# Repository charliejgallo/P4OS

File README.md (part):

# P4OS

An iPhone-style operating system for the
[**Waveshare ESP32-P4-WIFI6-Touch-LCD-5**](https://www.waveshare.com/esp32-p4-wifi6-touch-lcd-5.htm)
([wiki](https://docs.waveshare.com/ESP32-P4-WIFI6-Touch-LCD-5)). It is a 5"
720×1280 touch board with an ESP32-P4 (two RISC-V cores at 400 MHz and
32 MB of PSRAM) and an ESP32-C6 that does the Wi-Fi, the Bluetooth and,
since 0.34, the Zigbee radio.

It has a home screen with pages, folders and a dock, a control centre and
notifications, and a lock screen with an optional code, and it runs in
portrait or landscape. There are twenty-five built-in apps and, since
0.30, a **Store** that installs more than eighty others on the microSD,
loaded as shared objects:

- **A store of its own:** the board lists, installs and updates its apps
  from a catalogue published with each release, and fetches its own next
  firmware. Other people's repositories can be added beside the official
  one.

- **Games:** thirty-five, among them Mila (a Sokoban with a black cat in
  Blender 3D), Monster Hop, a racing game, golf, a robot RPG, a 3D pinball
  with six tables, a tower defense over ten worlds, a pipes game with six
  liquids, Doom at 35 fps and Duke Nukem 3D; and an emulator of
  fourteen consoles, the Game Boy Advance and the Neo Geo at full speed.
- **Tools:** notes with task lists, a street map with offline zones,
  internet radio, IP cameras, video, a 3D viewer, a tuner, a drawing app,
  a VNC viewer for a computer's screen, every 3D printer in the house
  (OctoPrint, PrusaLink, Bambu Lab, Klipper, Duet, Elegoo, FlashForge,
  Creality) with its camera, a computer algebra system with
  graphs, geometry and statistics, a data logger for the header's sensors,
  Lua, and Python (MicroPython).
- **A web portal** for files, updates, the log and the network sweeps, and a
  page for every app that wants one, which the app brings from the card;
  since 0.35 a phone on the portal is also a gamepad.
- **Messages, since 0.35:** Telegram with your own account (MTProto written
  in C), mail over IMAP and SMTP, a Meshtastic client, and **a Telegram bot
  of the board's own** that answers in a chat and sends what its rules say
  (a door opened, a screenshot at an hour). [docs/BOT.md](docs/BOT.md).
- **Cameras, since 0.35:** a USB webcam as a security camera that records
  H.264 when something moves and is an RTSP camera for Frigate, and as a
  camera that sees (faces, people, objects, hands, QR and barcodes) with
  Espressif's esp-dl on the board.
- **Bluetooth with the phone:** the iPhone's notifications on the board, in
  colour emoji, its music, and its calls answered or rejected from the
  board; and the board as a computer's wireless keyboard and mouse.
- **USB:** the port becomes a keyboard, mouse, gamepad, MIDI device, network
  or disk for a computer; and the board is a USB host on its 40-pin header,
  two ports at once: pendrives, keyboards, mice, gamepads, webcams, sound
  cards, MIDI and serial devices.
- **A Wi-Fi network of its own,** joined with a QR code.
- **Ethernet, for a board that has the module:** a W5500 on the header,
  and tools for a wired bench: a tester for a network port, finding a
  device of unknown address, a capture for Wireshark.
- **The workshop:** I2C, SPI, 1-Wire and GPIO on the 40-pin header, with
  112 kinds of sensor read by themselves (temperature, pressure, air
  quality, light, motion, current, distance...), addressable LED strips on
  any free pin (WLED's way), a serial terminal, an ESP32, Arduino and SWD programmer,
  RS485 with a Modbus tester (master, slave, monitor, a TCP gateway) and
  DMX512 (a test console, an analyzer, RDM, an Art-Net and sACN node, and a
  lighting console for a phone), a bench supply and scope, an EEPROM reader and writer, a PWM and
  servo generator with an analog level (and sixteen more servos on a
  PCA9685), a learning
  infrared remote with SmartIR's codes, a CAN bus analyser, and a logic
  analyser with ten protocol decoders for the 24 MHz USB boxes or an
  ESP32 with its own firmware. Each one was tried on the bench with real
  parts, wiring diagrams and photos included.
- **Zigbee, since 0.34:** the board is a **Zigbee hub** of its own, where
  almost any device can be joined and tried (sensors, relays, dimmers,
  Tuya devices, IR blasters), and it can **pose as a device** on Home
  Assistant's network (ZHA or Zigbee2MQTT) to test the coordinator; both
  from the board or from a phone through the portal. [More below](#zigbee-a-hub-a-test-bench-and-a-fake-device).
- **Drawn icons, since 0.34:** two packs, 3D toy and Line, as System parts
  in the Store; the usual circles stay a choice.
- **A software radio:** an RTL-SDR stick on the USB host gives a live
  spectrum and waterfall, broadcast FM in stereo, AM for the airband and
  narrow FM for hams and PMR, and the 433/868 MHz remotes and weather
  sensors decoded, with recordings of all of it and a page in the portal.

A desktop simulator runs the same UI code, so most of it can be built and
tried without the board.

It descends from [AmoledOS](https://github.com/charliejgallo/ESP32S3_AmoledOS),
a smartwatch firmware for a 1.8" board. The app model, the portal and many
of the apps came from there, redrawn for a screen five times larger.

<p align="center"><em>The captures come from the simulator, which draws the
same pixels as the board.</em></p>

## Getting started

A new board needs a cable once, and nothing after that.

1. **Flash it.** `esptool.py --chip esp32p4 chip_id` says which silicon the
   board has; download `p4os-rev1_3-full.zip` (chip v1.x) or
   `p4os-rev3_x-full.zip` (v3.x) from the
   [latest release](https://github.com/charliejgallo/P4OS/releases/latest),
   unpack it and, from inside the folder,
   `esptool.py --chip esp32p4 -p <port> write_flash @flash_args`.
2. **Put a microSD in**, formatted as FAT32. An empty one is fine.
3. **Join the Wi-Fi** in Settings → Networks, and pick the language.
4. **Open the Store** and get the apps you want. They install and open
   with no restart; a game's art comes in packs, the extra ones chosen on
   its page.
5. **Later versions arrive by themselves:** the Store updates the apps,
   and Settings → Update fetches the next firmware from GitHub, checks it
   and installs it on a tap.

| The Store | An app's page | Its description and extras | Settings, Update |
|---|---|---|---|
|  |  |  |  |

[docs/INSTALL.md](docs/INSTALL.md) is the whole of it, step by step: a new
board from nothing, a board coming from 0.2x, and adding apps.
[docs/STORE.md](docs/STORE.md) is the Store itself: what it checks, other
people's sources and what adding one means, and what a catalogue is made
of.

**Coming from 0.2x?** Update the firmware once more the old way (the
portal's Firmware page, with `p4os-<rev>.bin`). Nothing has to be copied to
the card: the apps that are there go on working, and Store → Installed
offers to take them over so they update from then on.

<p align="center"><em>And on the board: a BME280 on the rear header, found by
itself in Modules and by the scan in Bus, and the SPI loopback at 40 MHz
(that one is a capture from the panel, over HTTP).</em></p>

<p align="center"><em>A MAX6675 with a type K thermocouple on the SPI port:
Bus's example reads it, and Modules logs it every second; the curve is the
tip heated with a lighter.</em></p>

<p align="center"><em>A Pimoroni BME688 on i2c.ext: Bus lists what may live at
0x76, and Modules recognises it by itself as a BME688 (not a BME680), with
its gas resistance, which fell to half with alcohol near it and came back.</em></p>

<p align="center"><em>An SCD41 found by itself at 0x62: the chart is the CO2
of a breath on it, from 3000 ppm back to the room's 600.</em></p>

<p align="center"><em>The Programmer reading the whole flash of an AmoledOS
watch (an ESP32-S3 on its own USB) to the card, and writing it back: the
watch came back with every setting it had.</em></p>

<p align="center"><em>And by SWD, three wires to a Pico's debug header: the
RP2040 found behind its multidrop port and a new firmware written and
verified in under half a second.</em></p>

<p align="center"><em>A cheap Wi-Fi camera (a Hi3518EV200) opened up, its
console pads soldered to the header: U-Boot stopped with a mix of keys and its
16 MB read out through its own commands, twice, with the same SHA-256 -
the copy kept before giving it a new firmware.</em></p>

<p align="center"><em>The Ekoparty 2026 badge (an nRF52840 running
Meshtastic) read whole by SWD in 8 seconds, and an Arduino Nano from a
drawer on the USB host: written by the Programmer, then talking in the
Terminal.</em></p>

<p align="center"><em>A Blue Pill by SWD: its chip a clone (DPIDR 2BA01477,
a CKS32) with 128 KB that really are there. Read whole in a second, written
and erased; and the same again through ST's serial bootloader on the same
two wires.</em></p>

<p align="center"><em>An ESP32 DevKit on the header with six wires: the
board resets it into its ROM by itself and writes it at up to 921600 baud;
the Mac's esptool does the same through the board's bridge.</em></p>

<p align="center"><em>The same Nano, now on the header: its 5 V TX through
a divider, the EN line on its reset. Written and read by the Flasher, and
by avrdude on the Mac through the bridge.</em></p>

<p align="center"><em>A Mega 2560 from an old 3D printer and a Pro Micro on
the USB host: the Mega's own bootloader, and the Pro Micro's, reached with
the 1200-baud touch.</em></p>

<p align="center"><em>An Arduino Yún: its Linux in the Terminal through the
32U4, and its old U-Boot (no sf, no crc32, a big-endian MIPS) read whole by
the Programador, the same MD5 its Linux gives.</em></p>

<p align="center"><em>A WH5000 multimeter through its own USB cable (a
CP2102 inside), at 2400 baud: one line a reading, the digits on its
display. Any speed from 50 baud and any frame, 7E1 included, since
0.33.0.</em></p>

<p align="center"><em>Ethernet: a W5500 Lite on the header with six loose
wires, and Network's Cable tab telling what the port it is plugged into
gives (the network's addresses are blurred).</em></p>

---

## What it does

### The shell

The home screen has icon pages, folders, a dock and widgets.

- **Arranging it** is as on an iPhone. A long press starts edit mode, where
  a swipe still turns the page and an icon held still for a moment drags:
  - onto another page;
  - onto another app, to make a folder;
  - into a folder;
  - in or out of the dock, where the icons drag the same way.

  Folders show twelve apps a page, and a swipe turns one whole page. The
  portal's `#inicio` page does the same from a computer.

- **Widgets** (on the board since 0.22.0): edit mode's **+ Widget** adds
  the clock, the sensors, Home Assistant, the system monitor or Claude's
  usage; a tap on a widget opens its sheet, with its size (2×2, 4×2, 4×4),
  what it shows and a way to take it off, and one held still for a moment
  drags like an icon. The **sensors widget** shows up to six of the sensor
  service's values (on its own CO₂, temperature, humidity, pressure and the
  like; CO₂ and particles coloured by their level), the **Home Assistant**
  one up to eight entities, the favourites or the ones picked.

- **Swiping down** from the top opens the control centre (Wi-Fi, Bluetooth,
  do not disturb, the system sounds, orientation, brightness, volume, the
  music playing on the board or on the iPhone, the screen recording) and the
  notifications, with the phone's own actions.
- **System sounds:** a few notes of the speaker's bell when locking and
  unlocking, for notifications and calls, screenshots and recordings, and an
  optional keyboard click. The control centre's bell turns them all off.
- **Recording the screen** (since 0.21.5): the control centre's Grabar
  button records what the panel shows to an MP4 on the card (`/videos`),
  games and cameras included, with a red dot in the status bar while it
  runs. The P4's own engines do the work: the PPA turns each frame into
  the encoder's YUV, the hardware H.264 encoder compresses it (70 ms a
  frame between them, 15 fps on a quiet screen and 7-9 while apps move),
  and the CPU mostly waits. It plays on a Mac or a phone as it is.
- **Typing** (since 0.24.0): the field being edited shows a blinking cursor
  and a ring in the accent colour. The keyboard has an ñ, holding a key
  opens its accents (á, ü, ñ, ¿...), shift gives one capital or locks with
  two taps, and dragging along the space bar moves the cursor. Holding a
  field selects, cuts, copies and pastes; the clipboard is shared with the
  apps and with the portal, which can type a long password or an address
  straight into the field open on the board.
- **Search** (since 0.24.0): a swipe down from the middle of the home screen
  finds apps, the pages of Settings, notes by their text and the card's
  files, and works out a sum typed in.
- **The App Library** (since 0.35): the home screen's last page has every
  app, those taken off the home screen too, in the Store's categories: a
  card each with three apps big and a cluster of the rest that opens the
  whole category. Its pictures are made only while it is on screen.
- **The status bar** shows the Wi-Fi or the board's own network, the card
  and the USB, and the services working in the background: the Zigbee
  radio in a colour for each mode (its own network, open to join,
  emulating a device, scanning), the Telegram bot, Datalog logging, a 3D
  printer printing.
- **The orientation** is chosen in Settings or the control centre, because
  the board has no accelerometer. Apps that only make sense one way turn the
  screen while they are open.
- **The BOOT button** goes home with a tap and takes a screenshot with a long
  press; screenshots go to an album in Photos. Held during the boot screen,
  it starts in safe mode, without the card's apps.

| Settings in landscape | Macro pad | Photos |
|---|---|---|
|  |  |  |

<p align="center">
  
</p>

<p align="center"><em>Recorded by the board itself with its control
centre's button: the home screen, a folder, Photos.</em></p>

### The lock screen

It shows the time and date large, the messages that came in, and the music
playing with its buttons, over the wallpaper. To unlock, swipe up from
anywhere: the screen follows the finger.

- **When it locks:** at boot, and when the screen has been off for the time
  chosen in Settings (as soon as it goes off, or 1, 5, 15 or 60 minutes
  later). It is checked while the screen is still dark, so waking never
  shows a frame of what was under it.
- **An optional code** of 4 or 6 digits. It is kept as a salted SHA-256,
  never as itself. After 5 wrong tries the pad waits 30 s, and twice as long
  every 3 more; the count survives a restart.
- **A forgotten code:** in the BOOT button's safe mode the lock screen
  does not ask for it, and Settings can remove it.
- **Messages:** the notifications, the apps', the iPhone's over Bluetooth
  and Home Assistant's, in one list. With a code, their text can stay
  hidden until unlocked.
- **Widgets** (since 0.35): up to three capsules under the date, chosen in
  Settings, Lock screen: the next alarm, the sensors, the Zigbee network
  and its devices. Each shows only when it has something to say.

| Locked | With widgets | The code | Settings, Wi-Fi: its own network |
|---|---|---|---|
|  |  |  |  |

### Wallpapers

Eight gradients and a ninth that follows the time of day (night, dawn, day,
dusk, a little different every minute), and over them a photo from the card for the home screen
and another for the lock screen, chosen from Photos (the palette at the top
right of a photo). Each is cropped to the screen, kept in PSRAM (1.8 MB a
screen, nothing in internal RAM) and darkened as much as its own
brightness asks, once, while it is decoded, so the white names read on it
with no translucent layer to blend each frame. Turning the screen crops it
again; Settings, Wallpaper shows which photo each has and removes it.
The lock screen can take a whole folder instead (since 0.22.0): another of
its photos, at random, every time the board locks. The home screen's photo
stays in PSRAM with an app in front, so going home shows it at once; the
lock screen's is let go and decoded again as the screen goes dark.

| Home, over a photo | Locked, over another |
|---|---|
|  |  |

<p align="center"><em>Both on the board, both of Mila.</em></p>

The same page picks the **accent colour** (switches, selections, the active
buttons), one of iOS's nine system colours. The lock screen's clock is
large or medium, at the top or in the middle, and white, the accent, or the
lock photo's own colour lightened (Settings, Lock screen).

The gesture is a free swipe up, as phones do it today, and not a control
dragged along a track: Apple's 2005 patent on the latter
([US 7,657,849](https://patents.google.com/patent/US7657849B2)) expired in
2025, but that is not the reason this one was chosen.

### Built-in apps

Every day:

| Files | Photos | Music | Clock | Calendar |
|---|---|---|---|---|
|  |  |  |  |  |

| Calculator | Converter | Home Assistant | Claude | Monitor |
|---|---|---|---|---|
|  |  |  |  |  |

- **Files:** the card's explorer, with search, copy, move and folders;
  firmware opens straight in the Programmer, documents in Office and
  videos in Video.
- **Photos:** albums, the screenshots among them.
- **Music:** MP3, gapless, with the covers.
- **Clock:** world clock, alarms, stopwatch, timer and pomodoro.
- **Home Assistant:** favourites and the calendar, over its WebSocket API.
- **Claude:** the usage of your own Claude plan, the numbers Claude Code's
  `/usage` shows. It is unofficial; see [CLAUDE-APP.md](docs/CLAUDE-APP.md).
- **Monitor:** CPU per core, the tasks, memory, temperature and the network.
- **Bot** (since 0.35): the board's own Telegram bot, its token, the chats
  linked with a code, the commands it answers and the rules that make it
  write or act by itself ([docs/BOT.md](docs/BOT.md)).
- **Also built in:** MQTT, Conway's Life, and Network, which has its own
  section below.

### Network, the tools for a network

Red in Spanish. Seven tabs; the first four work over any network, the
next two are for the wire ([Ethernet](#connected)), and the last for both.

| Cable | The switch, the traffic | Device | One device | Lookout |
|---|---|---|---|---|
|  |  |  |  |  |

- **Ping, Hosts, WiFi, mDNS:** latency and loss charted; a sweep of the
  network with every MAC and its maker, and a port scan; the Wi-Fi
  channels; the services announced. Each sweep is saved, and the portal
  compares it with the one before.
- **Cable** (since 0.27): a tester for the network port the board is
  plugged into.
  - What the port gives: speed and duplex, the address, the DHCP server
    and its lease.
  - "Test the way out": the gateway, a name, the internet, one after the
    other.
  - The switch: a managed one says its name, the port and the VLAN this
    cable goes to (LLDP or CDP).
  - "Compare": ten pings to the gateway by the wire and ten by the Wi-Fi,
    side by side. "Measure the speed" counts what `iperf -c` sends from a
    computer.
  - "Capture to the card": every frame that reaches the port, in a pcap
    file for Wireshark, and a warning for what a network should not have:
    two DHCP servers, one address claimed twice, a broadcast storm.
- **Device** (Equipo, since 0.27): for a device plugged straight into the
  board, its address unknown.
  - It listens: a device gives itself away as it starts (ARP, DHCP, mDNS,
    NetBIOS, SSDP, WS-Discovery). A sweep by ARP of the networks devices
    come set to finds the one that says nothing.
  - A tap opens the device: everything it said, who made its network card
    (with the IEEE's register on the card), a ping, a scan of its ports,
    and "Get on its network", which gives the wire an address next to its
    own.
  - The bench network: the board gives addresses out by DHCP, serves
    files by TFTP, the time by NTP and takes the device's syslog, on the
    wire only. "Share the Wi-Fi" also gives the device a way out through
    the board's Wi-Fi.
- **Lookout** (Vigía, since 0.27): a list of the bench's devices, which
  are on (a ping or a TCP port, every ten seconds while the tab is open),
  and Wake-on-LAN for the ones that are off.

What ran on the board and what did not is under
[What was tested](#what-was-tested-and-what-not-yet);
[docs/MODULES.md](docs/MODULES.md), "Ethernet", has each tool.

### The workshop

The 40-pin rear header is described in `modules.txt`: which pins make each
port (`i2c.ext`, `spi.a`, `uart.*`, GPIO) and which modules hang from them.
While an app uses a port it owns it, and Settings, Expansion draws the
header with who holds each pin.

The whole header, pin by pin, is under [The hardware](#the-40-pin-header).

| Bus (I2C scan) | Modules | Terminal | Programmer | Equipos (Riden) | Electronics |
|---|---|---|---|---|---|
|  |  |  |  |  |  |

- **Bus:** scans I2C and names what answers, talks to SPI chips with presets
  (flash memories, the MAX31855 and MAX6675 thermocouples, the MCP3008, the
  RC522 RFID reader, a loopback), finds the DS18B20s on a 1-Wire bus and reads them live with
  their resolution, and reads and drives GPIO.
- **LED Strips:** an addressable strip (WS2812B, WS2811, SK6812, SK6812 RGBW)
  on any free pin of the header, with the colour order and the number of
  LEDs. It has 13 effects with speed, intensity and two colours. The power
  tab estimates what the strip draws, WLED's way, and dims the whole frame to
  stay within the supply's budget. The strip keeps running with the app
  closed and comes back after a restart.
- **Modules:** live readings from 112 kinds of sensor, every second with
  five minutes of history (since 0.20): temperature and humidity, pressure,
  air quality (CO2, VOC, particles), light and colour, motion and compass,
  voltage and current, distance and presence. The I2C ones that can tell
  who they are are found by themselves (BME280/680, SHT, AHT, SCD4x, SGP30,
  VEML7700, TSL2561, TCS34725, MPU-9250, BNO055, INA219/226/260, ADS1115,
  VL53L0X...); the rest are added from a form: thermocouples and PT100s on
  SPI, DS18B20s on 1-Wire, DHT22, HC-SR04, HX711 scales, flow meters and
  PIRs on plain pins, MH-Z19, PMS5003, PZEM-004T and LD2410 radars on a
  serial port. Every app reads them by name (`aos_sensors.h`); the
  catalogue is [docs/SENSORS.md](docs/SENSORS.md).
- **Terminal:** two serial ports, hex, filters and alerts; any speed from
  50 baud (300 to 2000000 in its list, any other typed in), any frame (8N1,
  7E1, 8O2...), and on a USB adapter DTR and RTS on or off, for the
  optical cables of multimeters.
- **Programmer:** flashes another ESP32 from firmware on the card
  (esp-serial-flasher), wired to the header or plugged into the USB host
  (a dev board goes into its bootloader by itself, through RTS and DTR);
  reads its flash to the card, to keep or to clone, and erases it. The
  same for an AVR Arduino through the bootloader it already has (Uno,
  Nano, Pro Mini, Mega, Leonardo, Micro), from the `.hex` the Arduino IDE
  exports. And by SWD, on the same pins: an nRF52, an RP2040, an RP2350,
  an STM32 (F0, F1, F2, F4 like the Black Pill, G0, G4, L4), a SAMD21 or
  SAMD51 (Arduino Zero and MKR, Adafruit M0 and M4, Seeed XIAO, their
  bootloader kept) or a SAM3X (an Arduino Due) written, verified and read
  to the card, its read protection taken off by erasing it, and the RTT
  console of the firmware running on it. Anything with U-Boot on a
  serial console - an IP camera, a router, a set-top box - has its
  whole flash read out through U-Boot's own commands, each piece checked
  by U-Boot's CRC, and nothing written. Or an STM32 through its own serial bootloader, with
  BOOT0 and NRST on the same lines an ESP32 uses. And it lends its port to
  the computer: esptool over `rfc2217://p4os.local:4000`, avrdude over
  `net:p4os.local:4001`; or becomes its CMSIS-DAP debug probe on the OTG
  connector, for OpenOCD, pyOCD and probe-rs. Its list of firmware on the
  card (since 0.28) takes 160, sorted by name, by the last added or by the
  last flashed, with a search, and says "versión nueva" when a folder or
  file is not what was last flashed under that name, by its content.
- **Modbus** (on the card since 0.25.0): a tester for Modbus RTU on RS485.
  A master (any function, once or live; find the units on a bus, and its
  speed and format, the format by the line's parity and framing errors),
  a slave with faults on demand (silent, slow, broken CRC, busy) that also
  serves Modbus TCP, and a monitor that only listens. Device profiles as
  CSV (six examples; Home Assistant and ESPHome YAML imported on the
  portal), so a master reads "Temperatura 23.4 °C" and a slave plays the
  device. A TCP → RTU gateway for a PC program or a SCADA, every frame in
  hex and in words, and the portal page drives it all.
- **Equipos:** the Riden RD60xx supply over RTU and a DOMCOM gateway, out
  of the old Modbus app.
- **DMX** (0.25.0): DMX512 on the same RS485 port. A test console (512
  faders, a chase to find channels, the packet's shape), a fixture the
  board plays, an analyzer with the BREAK and MAB measured on the pin, an
  Art-Net and sACN node (the network out as DMX, ArtPoll answered), and
  RDM: the fixtures on the line found by discovery, their address and name
  set, identify.
- **Luces** (0.25.0): a lighting console. Fixture types (twelve built in,
  more as CSV), a patch in four universes, a programmer for the selected
  fixtures (intensity, colour, strobe, a pan/tilt pad), groups, effects and
  three test modes, scenes with their own fade, a chase with tap tempo;
  universe 1 on RS485 and all of them as Art-Net. Its portal page is a
  second console for a phone.
- **Bench:** a Rigol scope over the LAN, the Riden, a UNI-T generator over
  USB, and a logger to CSV.
- **Electronics:** resistor colours, Ohm's law, dividers, LEDs, the 555 and
  SMD codes.

The simulator has fake chips and fake servers for all of it: every one of
the 112 sensors has an emulated twin that speaks its protocol
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
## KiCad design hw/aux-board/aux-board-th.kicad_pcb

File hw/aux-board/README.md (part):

# The auxiliary board for the 40-pin header

A board that plugs onto the header and takes each port of P4OS to a
connector with a name. The plan, the blocks and the two variants are in
[docs/plan/PCB.md](../../docs/plan/PCB.md) (Spanish); the pin map it follows
is [docs/img/pinout.svg](../../docs/img/pinout.svg).

**Where it stands (2026-11-12): a first schematic of both variants, a first
placement of their parts, the first tracks and a trial of the routing that
joined everything but four ground pads; nothing built. The outline
printed in plastic (`fit-test-th-print.svg`) was tried on the P4: the four
holes and the header fit.** Every part
value and footprint is a first choice to review against its datasheet.

- **th**, for a soldering iron: axial resistors, TO-92 transistors, every
  bridge a 2.54 mm jumper. The board is two layers, ordered bare.
- **smd**, for assembly at the factory: 0603 passives, SOT-23 transistors,
  solder bridges, a Qwiic socket and ESD protection on the USB lines. Its
  connectors are the same through-hole ones, soldered by hand afterwards.

RS485 and CAN are not on the board in either: their modules plug onto pin
headers (the automatic "RS485 to TTL" one on 3V3, TX, RX, GND; an
SN65HVD230 on 3V3, GND, CTX, CRX). Ethernet is a "W5500 Lite" module
(HW-884) on two sockets of six.

**There is no second 2x20 socket with the forty pins again** (taken out on
2026-11-11: nothing used it). In its place three headers of four pins:
switched 5 V and ground, 3.3 V and ground, and the three GPIO that no
other connector of the board carries, 35 (a strapping pin) and 37 and 38
(the console's UART). They stand above the 2x20, between the I2C headers
and the SPI one; beside the 2x20 there are only two bulk capacitors, the
5 V one next to its switch. The silkscreen names the header's forty pins
beside their solder joints.

**A second chip select for `spi.a`, by a jumper** (2026-11-15). The
Ethernet module holds the port's own chip select, GPIO49, so a second
chip on the same wires (an RC522, a thermocouple) needs another. JP17 is
three pins at the top of the 2x20, GPIO48 in the middle: the jumper on
`LED` gives it to the strip's terminal as before, on `CS2` to the SPI
header, which grew to 2x5 for it (CS2 and one more ground). A 10 k
resistor keeps CS2 high, its chip not chosen, while the jumper is on the
other side. In `modules.txt` that chip is `cs=48`. It is a pin header in
both variants: it is there to be moved. GPIO46 and 47, on the same
header, serve as chip selects too while no CAN module is on them.

**Supplies and ground are not to be routed thin:** 0.8 mm at least to the
5 V and 3.3 V headers and wherever it fits, 0.5 mm only through a passage
that takes no more. The ground planes join each ground pin by four spokes
of 0.8 mm.

## The Ethernet module's place

The module that answered on the bench (`docs/plan/ETHERNET.md`) has its
pins and its chip on one face and the RJ45 on the other, so on its sockets
it lies chip down with the RJ45 on top, its mouth to the board's right
edge. The silkscreen draws where it lies.

- The two rows are 20.32 mm apart (`ETH_ROWS` in `place.py`), measured.
- Pin 1 of each socket (G and GND) is the pin nearest the RJ45's mouth,
  as on the module. The row G, G, MO, SCK, CS, INT is the upper one.
- The first pin is 7.5 mm from the module's edge on the RJ45 side
  (`ETH_PIN1`), behind the module's two mounting holes: with it the
  module's edge is on the board's and the RJ45 sticks out past it. Found
  with the printed plate on 2026-11-12: the first guess, 2.5 mm read off
  photographs, left the sockets 5 mm too far out. **Tried again that
  evening on a second plate, with the module on it: its pins go into the
  two rows, the RJ45 comes out at the edge and the module's board does not
  stick out past the plate.**
- Under the module there are 8.5 mm (the sockets' height): a resistor, a
  small capacitor or SMD parts fit, a pin header or an electrolytic do
  not. `place.py` refuses a tall part there.

| File | What it is |
|---|---|
| `gen.py` | the board as a list: its parts and the net on each pin, for the two variants |
| `kisch.py` | writes a KiCad schematic from that list, with KiCad's own symbols |
| `aux-board-th.kicad_sch`, `aux-board-smd.kicad_sch` | the schematics, generated: open them in KiCad 10 |
| `place.py` | puts those parts on a board with the P4's outline and holes, with their nets and the silkscreen; it runs under KiCad's Python |
| `aux-board-th.kicad_pcb`, `aux-board-smd.kicad_pcb` | those boards, generated: drafts to look at and to move, with the first tracks (below) |
| `paper-th.svg` | the through-hole board's front at its real size, outline, lettering and pads: printed on paper at 100 %, it is laid on the P4 and the parts are stood on it |
| `autoroute.py` | a trial router: routes the generated board to show where it is hard ("A trial of the routing", below) |
| `fit-test-th.svg`, `fit-test-th-print.svg` | the through-hole board's outline with every hole, 1 unit = 1 mm: a slicer extrudes it into a plate to try the fit on the P4. The second has each hole 0.4 mm wider, for a printer that closes small holes |

| Through-hole | SMD |
|---|---|
|  |  |

*The drafts as KiCad renders them, black as they would be ordered. The
board is the size of the P4's own and sits on its four holes. The
silkscreen names every connector, every pin and every bridge; where each
part goes is a first guess. `place.py` refuses a placement where two parts
overlap or one leaves the board (the USB sockets overhang on purpose).*

## The tracks so far

`place.py` lays what needs no choice, and lays it again every time it runs:

- **A fan-out of the 2x20 header on the front:** every pin that is not
  ground leaves to a column just right of the header, the inner row
  straight and the outer row through the gap above its own row (0.25 mm,
  0.4 mm for 5 V and 3.3 V).
- **Under the header, the back takes no track and no via** (a KiCad rule
  area): the ground pins reach the back plane by the strip each side of
  the two rows.
- **A ground plane on each face.** The files keep the planes unfilled
  (filled, each file is more than twice the size): KiCad fills them with B.

It then asks KiCad for its design rule check on a copy with the planes
filled, and prints what is left:

    routed: 47 track segments and two ground planes; still to join: 118 connections
    design rules: silk_edge_clearance x4, track_dangling x32

Ground is joined everywhere by the planes; 118 connections of the other
53 nets are still to route (128 on the SMD variant). The four silkscreen
warnings are the USB sockets' outlines, which overhang the edge on
purpose, and the 32 dangling tracks are the fan-out, which goes nowhere
yet.

**The boards are generated, so a track drawn by hand in KiCad is lost the
next time `place.py` runs.** While parts are still moving, tracks go in
the script; routing by hand starts once the placement is frozen, and from
then on `place.py` is not run again.

## A trial of the routing (2026-11-12, the router redone on 2026-11-13)

`autoroute.py` routes the generated board by itself, to find where the
placement is hard before anyone routes it for real. It runs under KiCad's
Python in about three minutes and writes `trial-th.kicad_pcb` or
`trial-smd.kicad_pcb`, which are not kept in git: open them in KiCad to
look.

    <KiCad's python3> hw/aux-board/autoroute.py th

It is a maze router on a 0.3175 mm grid that starts on the header's
pin 1: 0.25 mm tracks, 0.8 mm for the supplies (0.5 mm, then 0.25 mm,
where 0.8 finds no room; it says where), 0.6 mm vias, KiCad's default
0.2 mm clearance.

- **The nets negotiate.** Routed one after another, each around the ones
  before, the last nets went the long way round: tracks along the board's
  edges, 94 mm over the direct way for one of them. Now every net is
  first routed as if alone, crossing the others at a price. Then the ones
  that cross are routed again, round after round, while that price goes
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
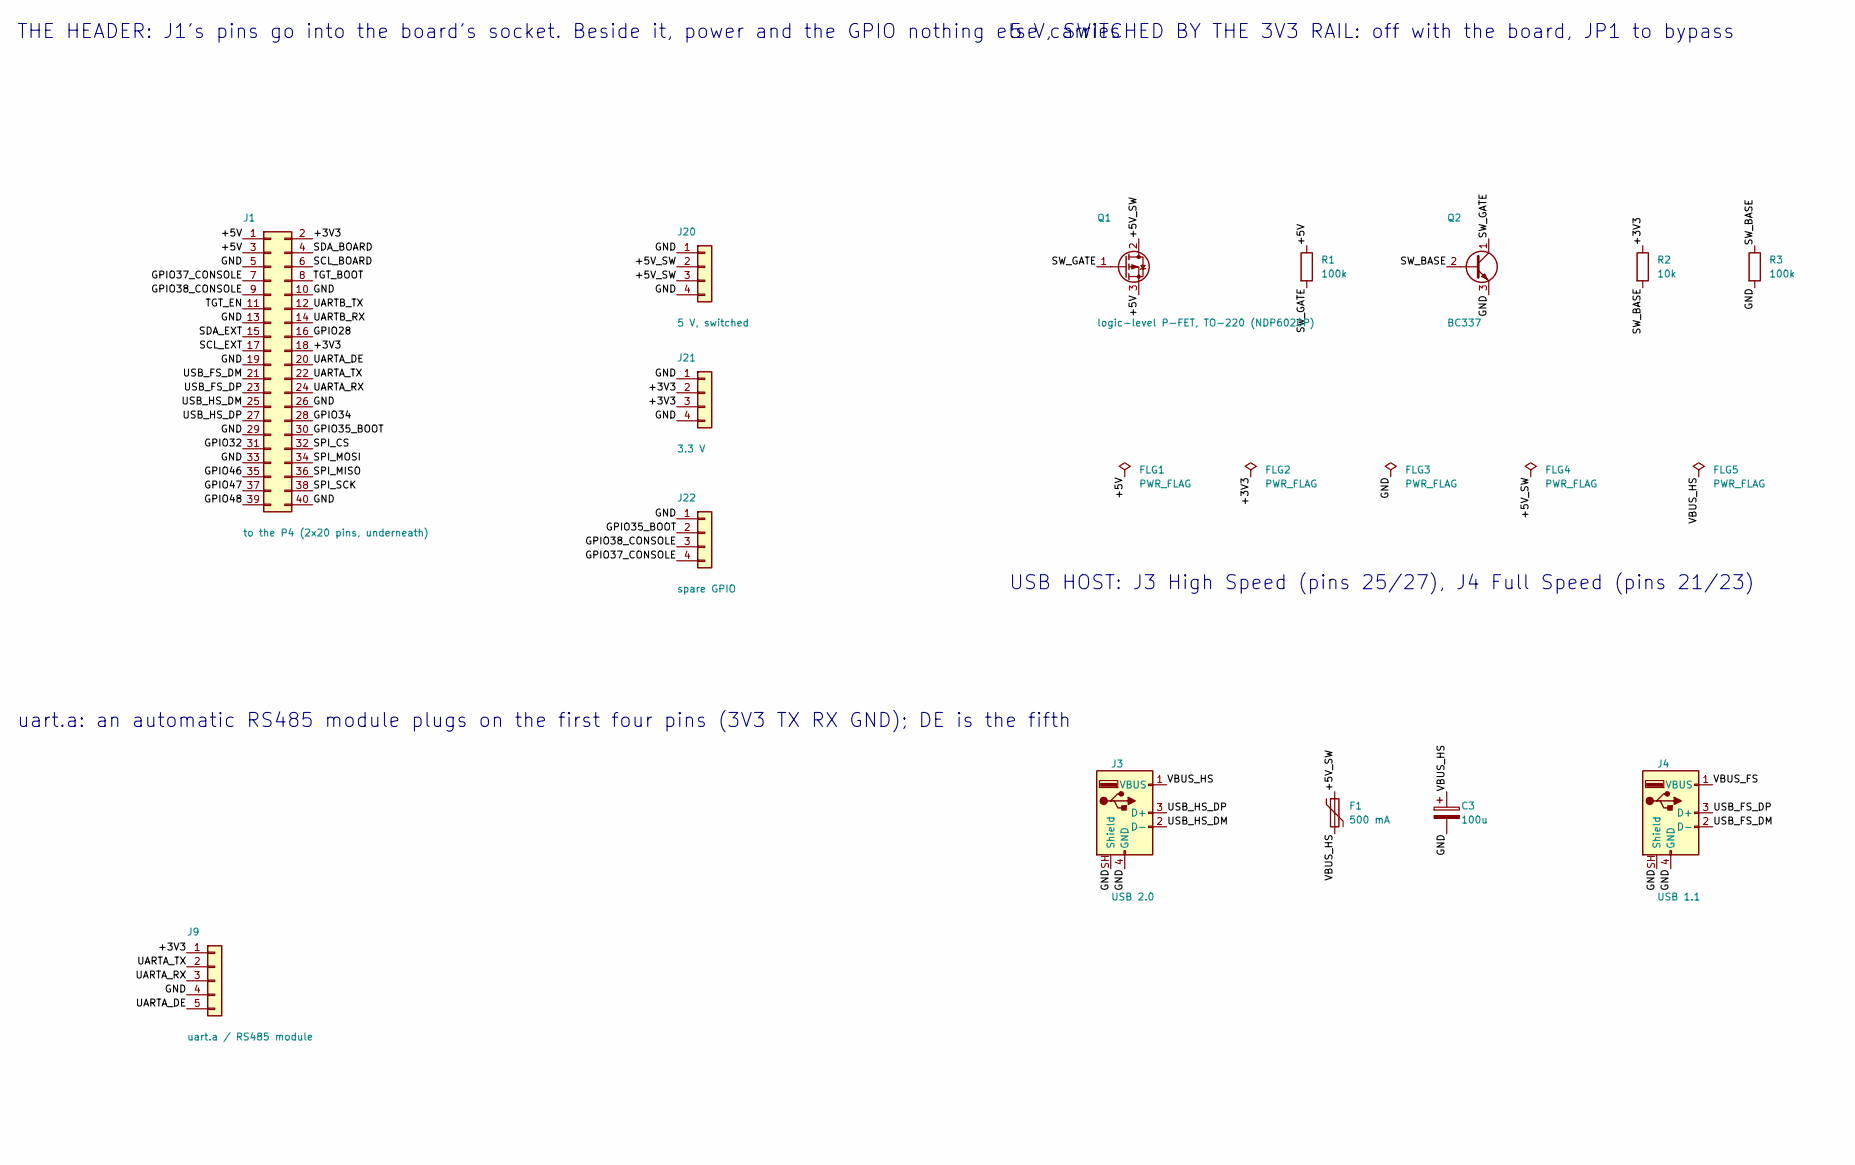
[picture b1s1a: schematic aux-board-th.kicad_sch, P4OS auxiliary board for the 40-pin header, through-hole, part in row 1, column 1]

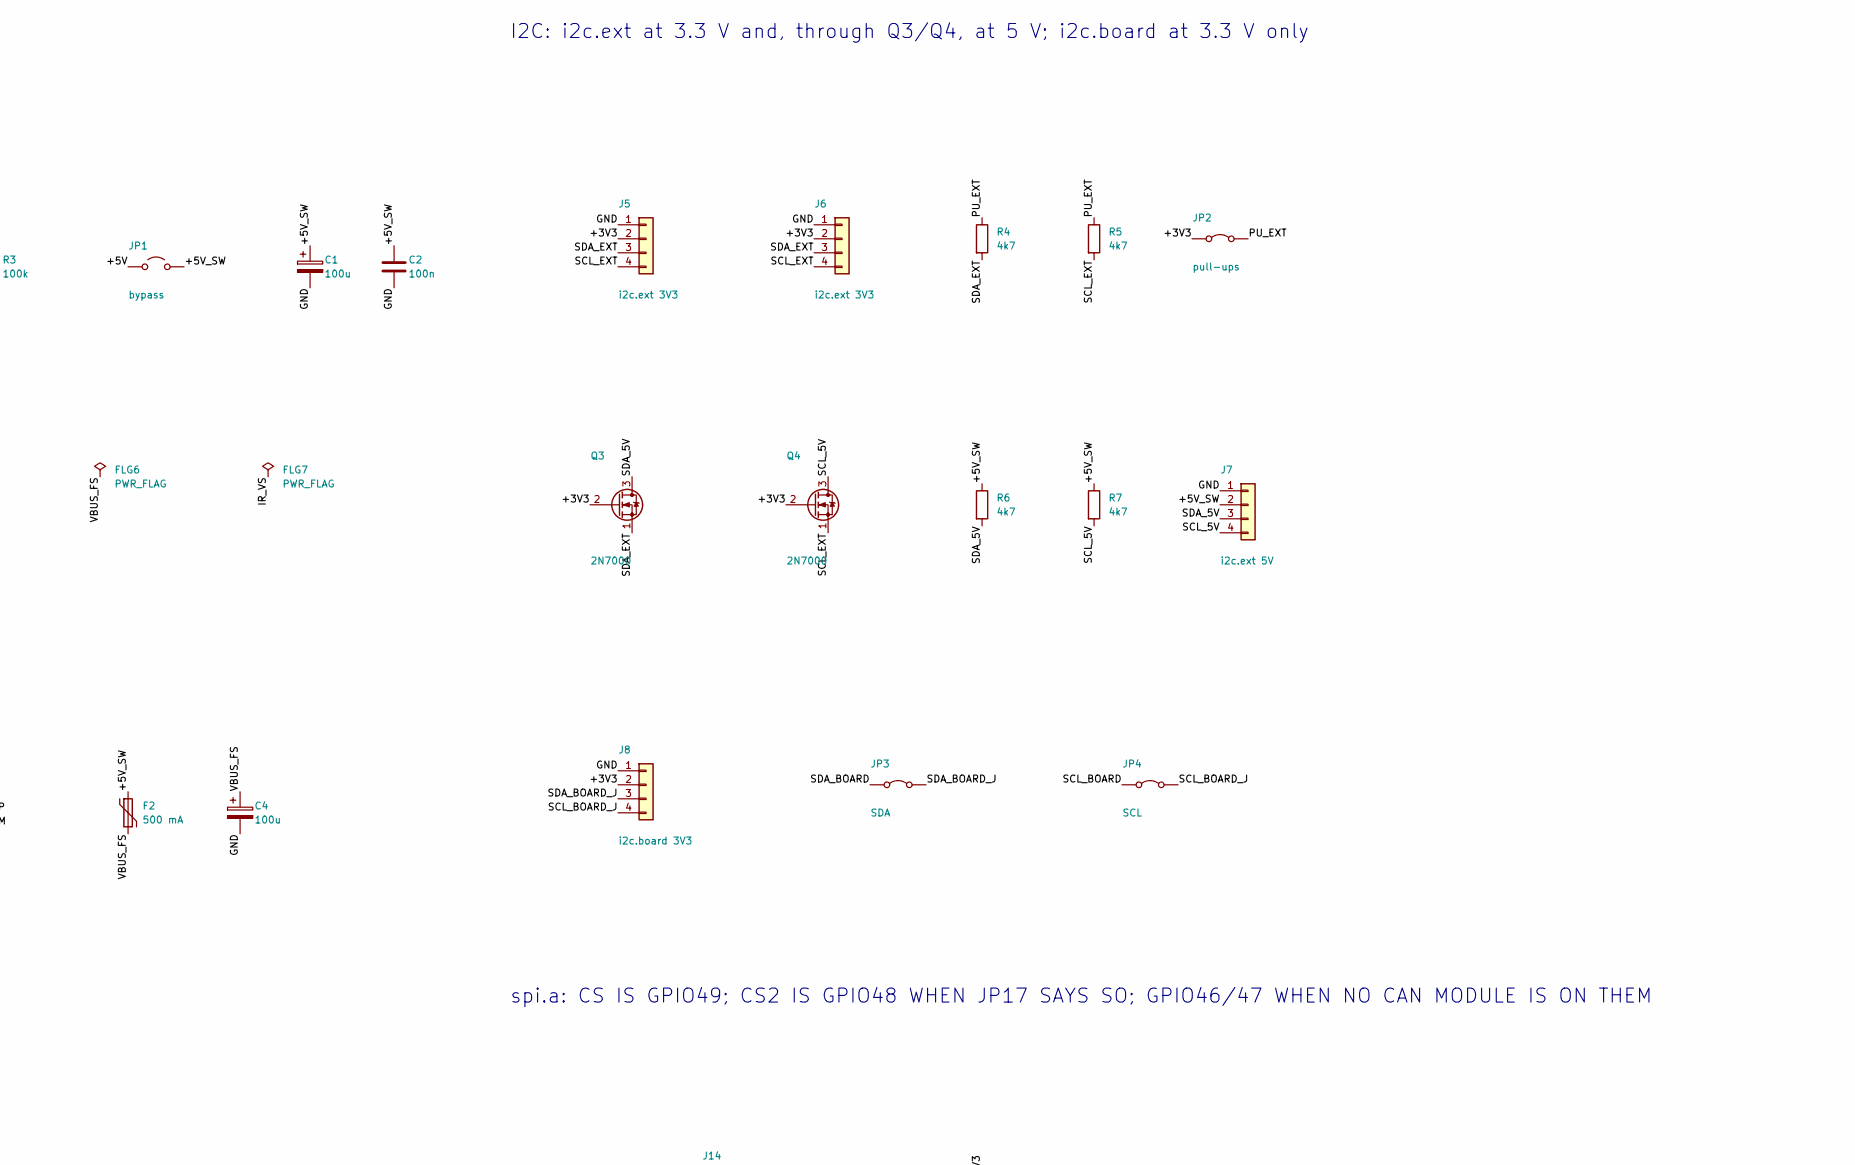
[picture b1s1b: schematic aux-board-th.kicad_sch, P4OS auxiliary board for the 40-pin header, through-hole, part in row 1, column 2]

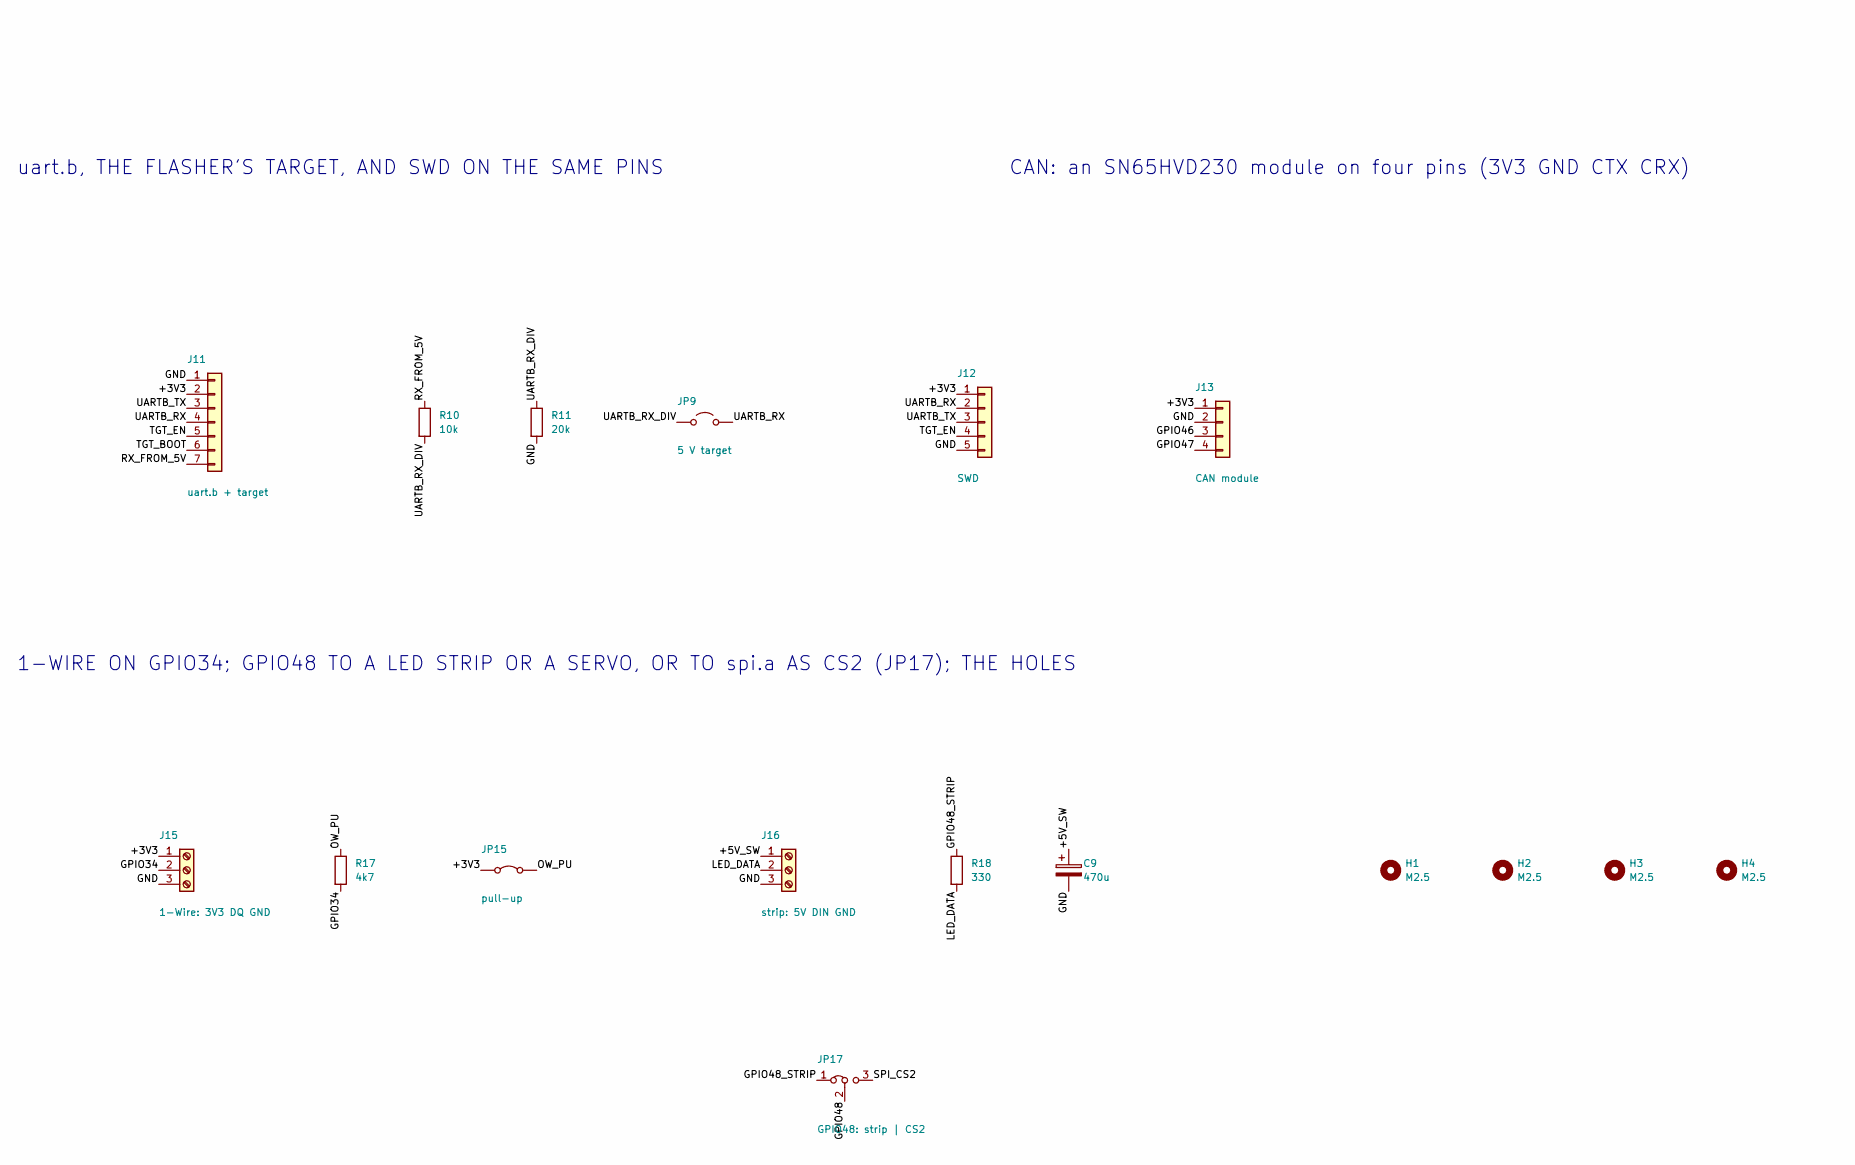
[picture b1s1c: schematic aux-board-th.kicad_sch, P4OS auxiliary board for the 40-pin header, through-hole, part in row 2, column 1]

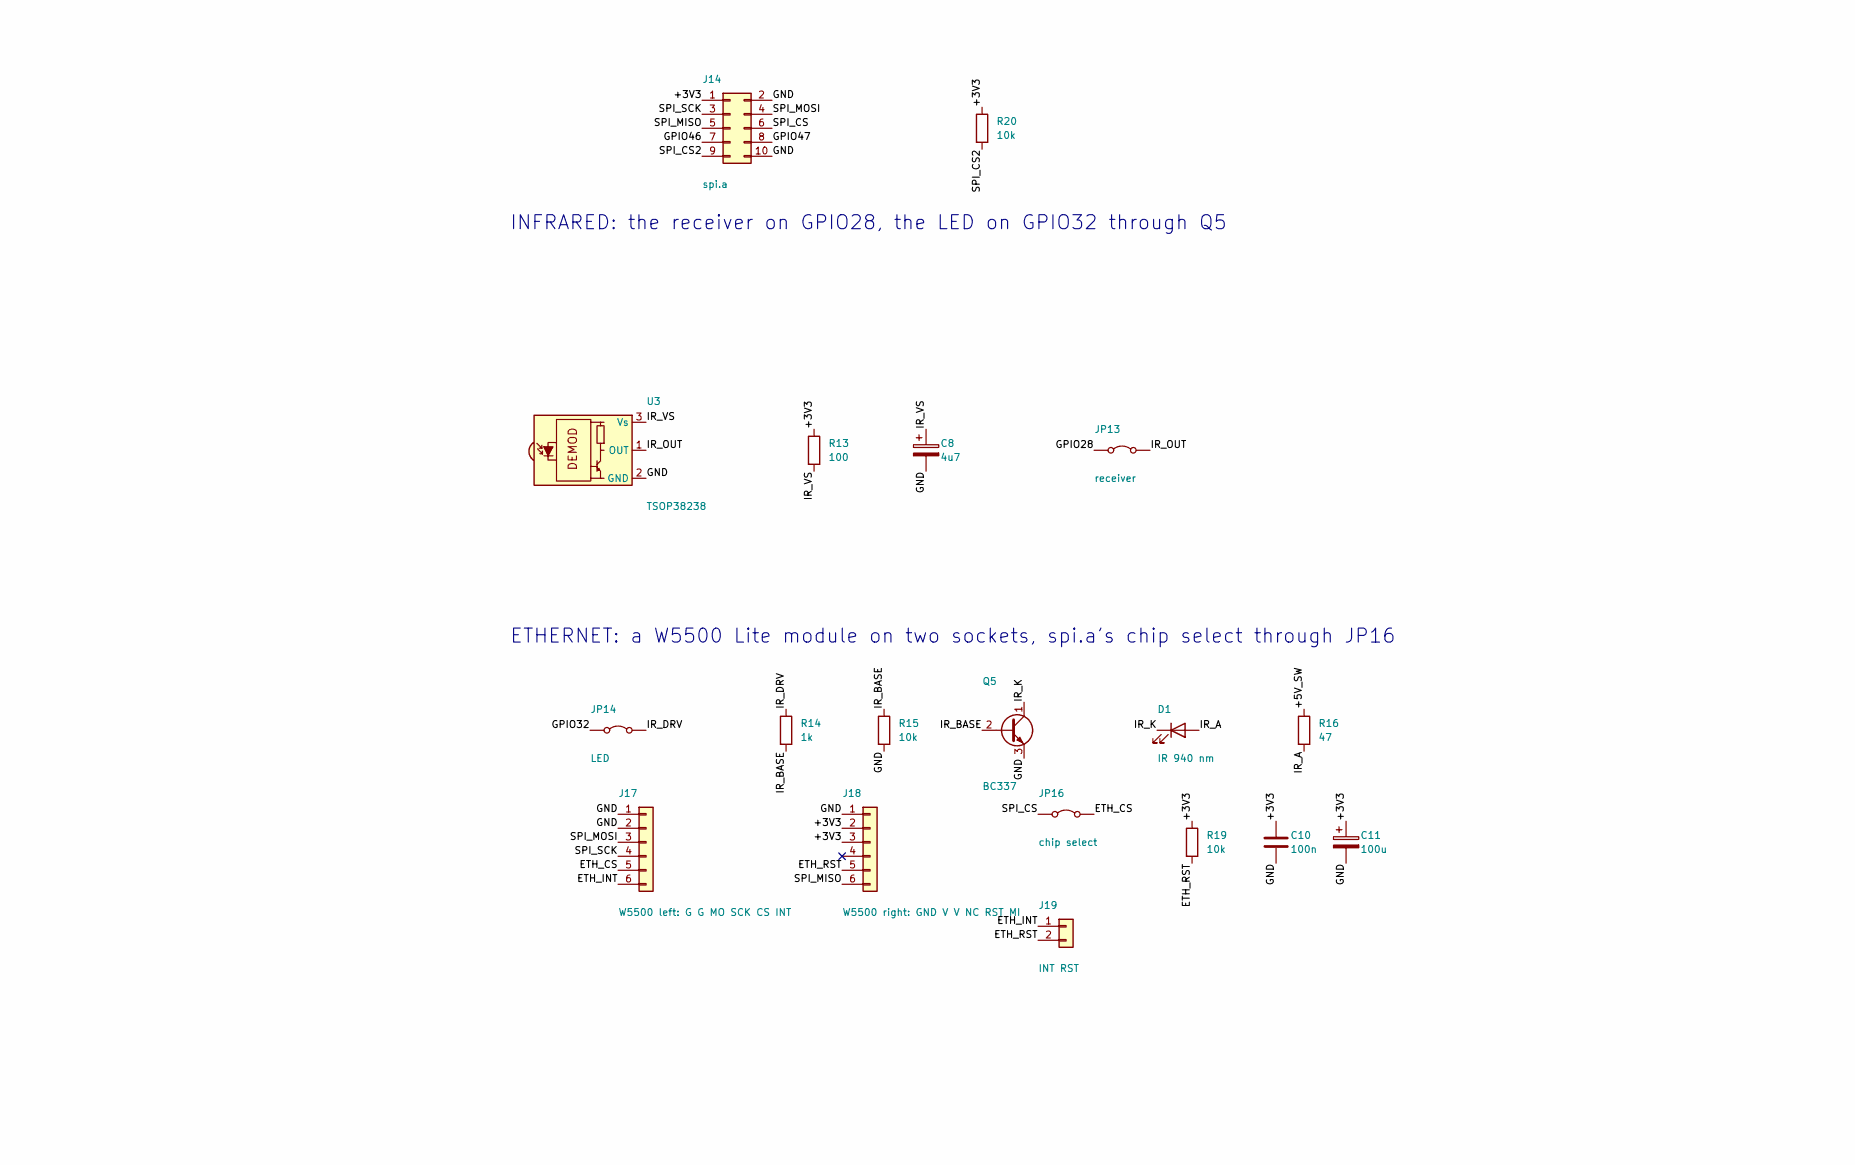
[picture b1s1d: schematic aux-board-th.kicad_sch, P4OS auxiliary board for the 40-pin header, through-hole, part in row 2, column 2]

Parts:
C1, C3, C4, C11: 100u; CP_Radial_D6.3mm_P2.50mm
C2, C10: 100n; C_Disc_D5.0mm_W2.5mm_P5.00mm
C8: 4u7; CP_Radial_D6.3mm_P2.50mm
C9: 470u; CP_Radial_D8.0mm_P3.50mm
D1: IR 940 nm; LED_D5.0mm
F1, F2: 500 mA; Fuse_Bourns_MF-RG300
FLG1, FLG2, FLG3, FLG4, FLG5, FLG6, FLG7: PWR_FLAG
H1, H2, H3, H4: M2.5; MountingHole_2.7mm_M2.5
J1: to the P4 (2x20 pins, underneath); PinHeader_2x20_P2.54mm_Vertical
J3: USB 2.0; USB_A_Molex_67643_Horizontal
J4: USB 1.1; USB_A_Molex_67643_Horizontal
J5, J6: i2c.ext 3V3; PinHeader_1x04_P2.54mm_Vertical
J7: i2c.ext 5V; PinHeader_1x04_P2.54mm_Vertical
J8: i2c.board 3V3; PinHeader_1x04_P2.54mm_Vertical
J9: uart.a / RS485 module; PinHeader_1x05_P2.54mm_Vertical
J11: uart.b + target; PinHeader_1x07_P2.54mm_Vertical
J12: SWD; PinHeader_1x05_P2.54mm_Vertical
J13: CAN module; PinHeader_1x04_P2.54mm_Vertical
J14: spi.a; PinHeader_2x05_P2.54mm_Vertical
J15: 1-Wire: 3V3 DQ GND; TerminalBlock_Phoenix_MKDS-1,5-3-5.08_1x03_P5.08mm_Horizont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
J16: strip: 5V DIN GND; TerminalBlock_Phoenix_MKDS-1,5-3-5.08_1x03_P5.08mm_Horizont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
J17: W5500 left: G G MO SCK CS INT; PinSocket_1x06_P2.54mm_Vertical
J18: W5500 right: GND V V NC RST MI; PinSocket_1x06_P2.54mm_Vertical
J19: INT RST; PinHeader_1x02_P2.54mm_Vertical
J20: 5 V, switched; PinHeader_1x04_P2.54mm_Vertical
J21: 3.3 V; PinHeader_1x04_P2.54mm_Vertical
J22: spare GPIO; PinHeader_1x04_P2.54mm_Vertical
JP1: bypass; PinHeader_1x02_P2.54mm_Vertical
JP2: pull-ups; PinHeader_1x02_P2.54mm_Vertical
JP3: SDA; PinHeader_1x02_P2.54mm_Vertical
JP4: SCL; PinHeader_1x02_P2.54mm_Vertical
JP9: 5 V target; PinHeader_1x02_P2.54mm_Vertical
JP13: receiver; PinHeader_1x02_P2.54mm_Vertical
JP14: LED; PinHeader_1x02_P2.54mm_Vertical
JP15: pull-up; PinHeader_1x02_P2.54mm_Vertical
JP16: chip select; PinHeader_1x02_P2.54mm_Vertical
JP17: GPIO48: strip | CS2; PinHeader_1x03_P2.54mm_Vertical
Q1: logic-level P-FET, TO-220 (NDP6020P); TO-220-3_Vertical
Q2, Q5: BC337; TO-92_Inline
Q3, Q4: 2N7000; TO-92_Inline
R1, R3: 100k; R_Axial_DIN0207_L6.3mm_D2.5mm_P10.16mm_Horizontal
R2, R10, R15, R19, R20: 10k; R_Axial_DIN0207_L6.3mm_D2.5mm_P10.16mm_Horizontal
R4, R5, R6, R7, R17: 4k7; R_Axial_DIN0207_L6.3mm_D2.5mm_P10.16mm_Horizontal
R11: 20k; R_Axial_DIN0207_L6.3mm_D2.5mm_P10.16mm_Horizontal
R13: 100; R_Axial_DIN0207_L6.3mm_D2.5mm_P10.16mm_Horizontal
R14: 1k; R_Axial_DIN0207_L6.3mm_D2.5mm_P10.16mm_Horizontal
R16: 47; R_Axial_DIN0207_L6.3mm_D2.5mm_P10.16mm_Horizontal
R18: 330; R_Axial_DIN0207_L6.3mm_D2.5mm_P10.16mm_Horizontal
U3: TSOP38238; Vishay_MINICAST-3Pin

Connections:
+3V3: C10.1, C11.1, FLG2.1, J1.2, J1.18, J5.2, J6.2, J8.2, J9.1, J11.2, J12.1, J13.1, J14.1, J15.1, J18.2, J18.3, J21.2, J21.3, JP2.1 (A), JP15.1 (A), Q3.2 (G), Q4.2 (G), R2.1, R13.1, R19.1, R20.1
+5V: FLG1.1, J1.1, J1.3, JP1.1 (A), Q1.3 (S), R1.1
+5V_SW: C1.1, C2.1, C9.1, F1.1, F2.1, FLG4.1, J7.2, J16.1, J20.2, J20.3, JP1.2 (B), Q1.2 (D), R6.1, R7.1, R16.1
ETH_CS: J17.5, JP16.2 (B)
ETH_INT: J17.6, J19.1
ETH_RST: J18.5, J19.2, R19.2
GND: C1.2, C2.2, C3.2, C4.2, C8.2, C9.2, C10.2, C11.2, FLG3.1, J1.5, J1.10, J1.13, J1.19, J1.26, J1.29, J1.33, J1.40, J3.4 (GND), J3.SH (Shield), J4.4 (GND), J4.SH (Shield), J5.1, J6.1, J7.1, J8.1, J9.4, J11.1, J12.5, J13.2, J14.2, J14.10, J15.3, J16.3, J17.1, J17.2, J18.1, J20.1, J20.4, J21.1, J21.4, J22.1, Q2.3 (E), Q5.3 (E), R3.2, R11.2, R15.2, U3.2 (GND)
GPIO28: J1.16, JP13.1 (A)
GPIO32: J1.31, JP14.1 (A)
GPIO34: J1.28, J15.2, R17.2
GPIO35_BOOT: J1.30, J22.2
GPIO37_CONSOLE: J1.7, J22.4
GPIO38_CONSOLE: J1.9, J22.3
GPIO46: J1.35, J13.3, J14.7
GPIO47: J1.37, J13.4, J14.8
GPIO48: J1.39, JP17.2 (C)
GPIO48_STRIP: JP17.1 (A), R18.1
IR_A: D1.2 (A), R16.2
IR_BASE: Q5.2 (B), R14.2, R15.1
IR_DRV: JP14.2 (B), R14.1
IR_K: D1.1 (K), Q5.1 (C)
IR_OUT: JP13.2 (B), U3.1 (OUT)
IR_VS: C8.1, FLG7.1, R13.2, U3.3 (Vs)
LED_DATA: J16.2, R18.2
OW_PU: JP15.2 (B), R17.1
PU_EXT: JP2.2 (B), R4.1, R5.1
RX_FROM_5V: J11.7, R10.1
SCL_5V: J7.4, Q4.3 (D), R7.2
SCL_BOARD: J1.6, JP4.1 (A)
SCL_BOARD_J: J8.4, JP4.2 (B)
SCL_EXT: J1.17, J5.4, J6.4, Q4.1 (S), R5.2
SDA_5V: J7.3, Q3.3 (D), R6.2
SDA_BOARD: J1.4, JP3.1 (A)
SDA_BOARD_J: J8.3, JP3.2 (B)
SDA_EXT: J1.15, J5.3, J6.3, Q3.1 (S), R4.2
SPI_CS: J1.32, J14.6, JP16.1 (A)
SPI_CS2: J14.9, JP17.3 (B), R20.2
SPI_MISO: J1.36, J14.5, J18.6
SPI_MOSI: J1.34, J14.4, J17.3
SPI_SCK: J1.38, J14.3, J17.4
SW_BASE: Q2.2 (B), R2.2, R3.1
SW_GATE: Q1.1 (G), Q2.1 (C), R1.2
TGT_BOOT: J1.8, J11.6
TGT_EN: J1.11, J11.5, J12.4
UARTA_DE: J1.20, J9.5
UARTA_RX: J1.24, J9.3
UARTA_TX: J1.22, J9.2
UARTB_RX: J1.14, J11.4, J12.2, JP9.2 (B)
UARTB_RX_DIV: JP9.1 (A), R10.2, R11.1
UARTB_TX: J1.12, J11.3, J12.3
USB_FS_DM: J1.21, J4.2 (D-)
USB_FS_DP: J1.23, J4.3 (D+)
USB_HS_DM: J1.25, J3.2 (D-)
USB_HS_DP: J1.27, J3.3 (D+)
VBUS_FS: C4.1, F2.2, FLG6.1, J4.1 (VBUS)
VBUS_HS: C3.1, F1.2, FLG5.1, J3.1 (VBUS)

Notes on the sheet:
THE HEADER: J1's pins go into the board's socket. Beside it, power and the GPIO nothing else carries
5 V, SWITCHED BY THE 3V3 RAIL: off with the board, JP1 to bypass
USB HOST: J3 High Speed (pins 25/27), J4 Full Speed (pins 21/23)
I2C: i2c.ext at 3.3 V and, through Q3/Q4, at 5 V; i2c.board at 3.3 V only
uart.a: an automatic RS485 module plugs on the first four pins (3V3 TX RX GND); DE is the fifth
uart.b, THE FLASHER'S TARGET, AND SWD ON THE SAME PINS
CAN: an SN65HVD230 module on four pins (3V3 GND CTX CRX)
spi.a: CS IS GPIO49; CS2 IS GPIO48 WHEN JP17 SAYS SO; GPIO46/47 WHEN NO CAN MODULE IS ON THEM
ETHERNET: a W5500 Lite module on two sockets, spi.a's chip select through JP16
INFRARED: the receiver on GPIO28, the LED on GPIO32 through Q5
1-WIRE ON GPIO34; GPIO48 TO A LED STRIP OR A SERVO, OR TO spi.a AS CS2 (JP17); THE HOLES

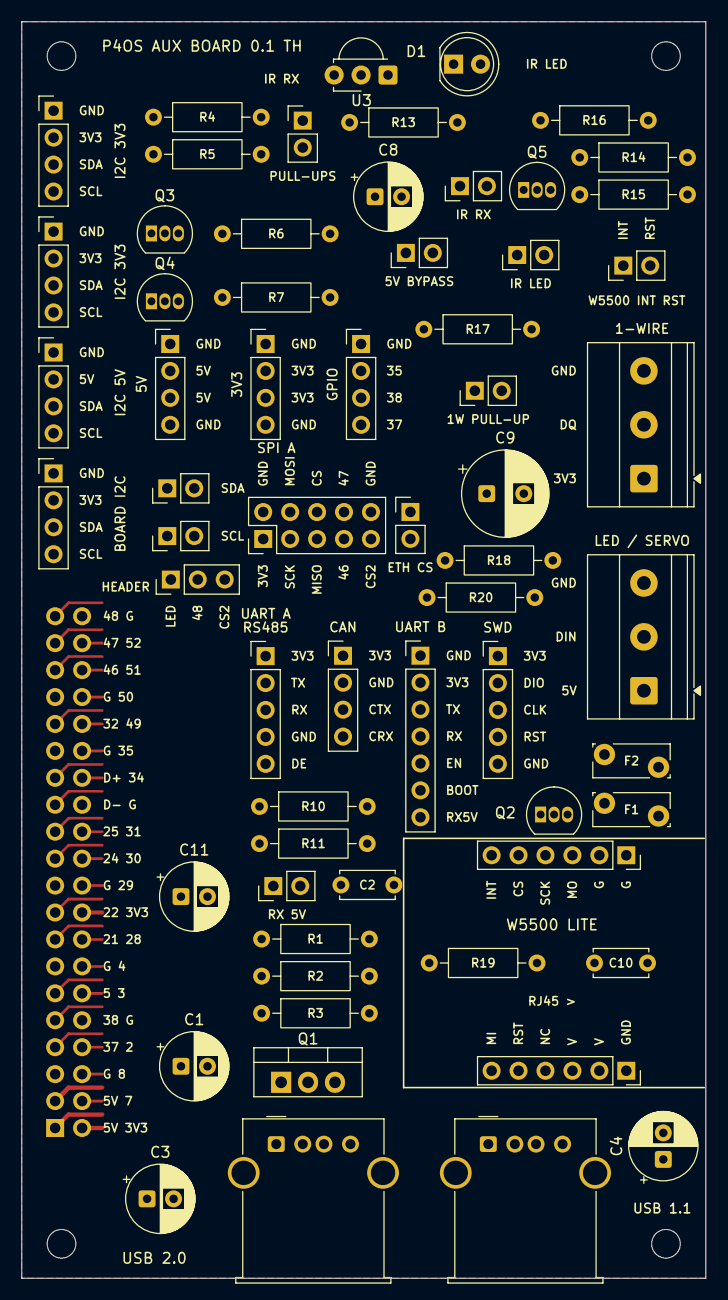
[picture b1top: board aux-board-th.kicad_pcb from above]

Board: 2 copper layers, 64.5 x 118.5 mm, 68 parts (1 on the bottom side), 56 nets.

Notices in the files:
README.md:
Licence:
MIT, see [LICENSE](LICENSE). Third-party code, fonts, icons and data keep
their own licences; [THIRD-PARTY.md](THIRD-PARTY.md) lists each one and what
it asks for. `apps/doom/` is Chocolate Doom through doomgeneric, under the
GNU GPL v2, and no WAD is included. `apps/duke3d/` is Chocolate Duke3D, under
the GNU GPL v2 and, for its Build engine, Ken Silverman's Build licence; no
GRP is included. `apps/emulador/` keeps each console's core in its own
module under that core's licence (GPL, AGPL, and two non-commercial:
Snes9x and the Mega Drive's Z80), listed in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
